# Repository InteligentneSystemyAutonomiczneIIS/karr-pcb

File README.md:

# karr-pcb
PCB for autonomus city simulation project

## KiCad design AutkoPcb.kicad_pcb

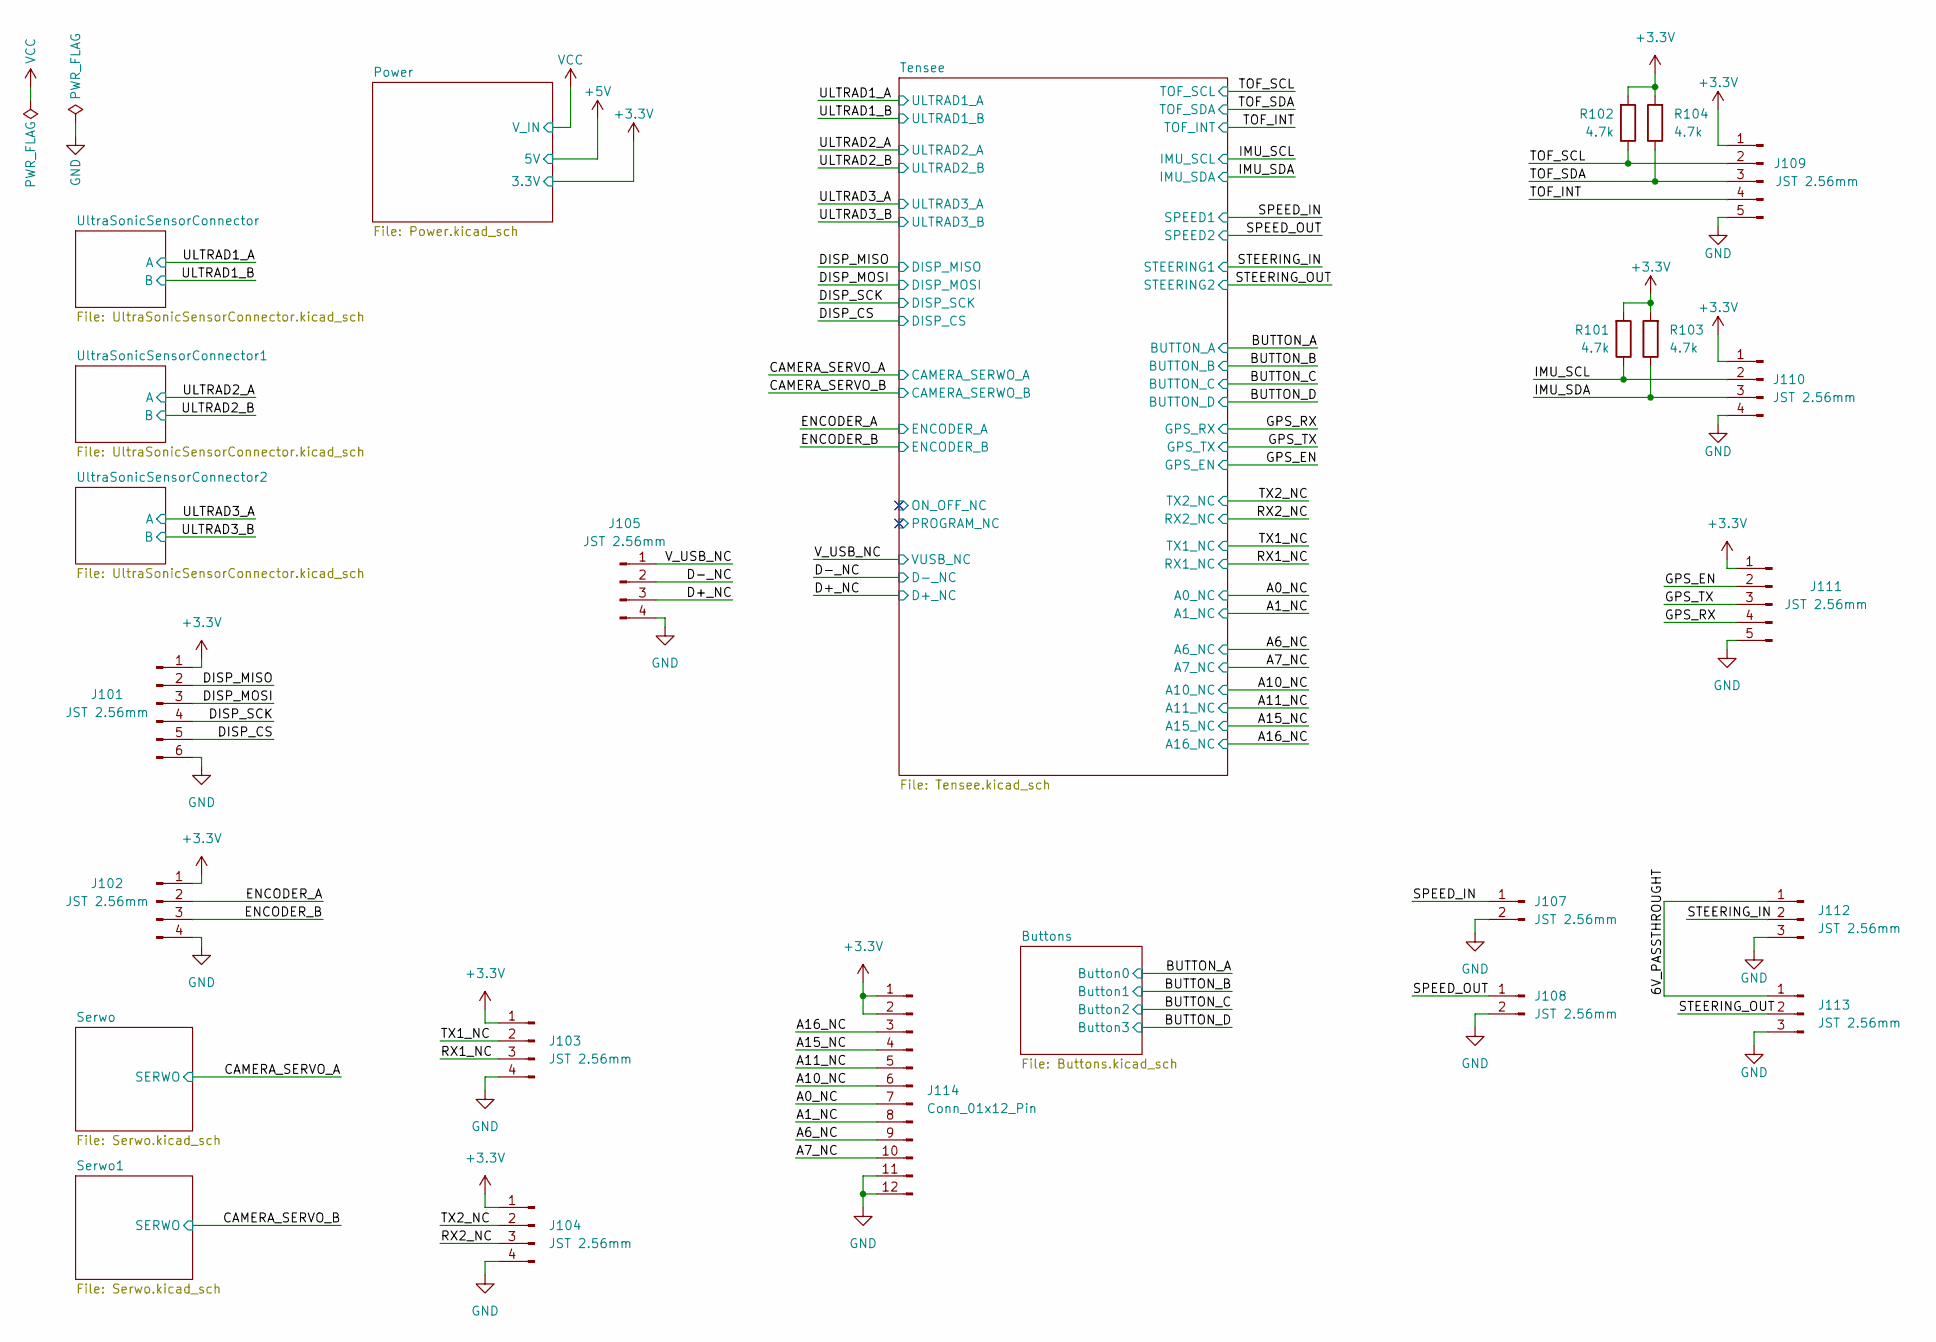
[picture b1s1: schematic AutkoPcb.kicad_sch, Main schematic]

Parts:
J101: JST 2.56mm; JST_XA_B06B-XASK-1_1x06_P2.50mm_Vertical
J102, J105, J110: JST 2.56mm; JST_XH_B4B-XH-A_1x04_P2.50mm_Vertical
J103, J104: JST 2.56mm; PinHeader_1x04_P2.54mm_Vertical
J107, J108: JST 2.56mm; JST_XH_B2B-XH-A_1x02_P2.50mm_Vertical
J109, J111: JST 2.56mm; JST_XH_B5B-XH-A_1x05_P2.50mm_Vertical
J112, J113: JST 2.56mm; JST_XH_B3B-XH-A_1x03_P2.50mm_Vertical
J114: Conn_01x12_Pin; PinSocket_1x12_P2.54mm_Vertical
R101, R102, R103, R104: 4.7k; R_Axial_DIN0204_L3.6mm_D1.6mm_P7.62mm_Horizontal

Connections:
+3.3V: J101.1, J102.1, J103.1, J104.1, J109.1, J110.1, J111.1, J114.1, J114.2, R101.2, R102.2, R103.2, R104.2; also elsewhere on the board
/6V_PASSTHROUGHT: J112.1, J113.1
/A0_NC: J114.7; also elsewhere on the board
/A1_NC: J114.8; also elsewhere on the board
/A6_NC: J114.9; also elsewhere on the board
/A7_NC: J114.10; also elsewhere on the board
/A10_NC: J114.6; also elsewhere on the board
/A11_NC: J114.5; also elsewhere on the board
/A15_NC: J114.4; also elsewhere on the board
/A16_NC: J114.3; also elsewhere on the board
/D+_NC: J105.3; also elsewhere on the board
/D-_NC: J105.2; also elsewhere on the board
/DISP_CS: J101.5; also elsewhere on the board
/DISP_MISO: J101.2; also elsewhere on the board
/DISP_MOSI: J101.3; also elsewhere on the board
/DISP_SCK: J101.4; also elsewhere on the board
/ENCODER_A: J102.2; also elsewhere on the board
/ENCODER_B: J102.3; also elsewhere on the board
/GPS_EN: J111.2; also elsewhere on the board
/GPS_RX: J111.4; also elsewhere on the board
/GPS_TX: J111.3; also elsewhere on the board
/IMU_SCL: J110.2, R101.1; also elsewhere on the board
/IMU_SDA: J110.3, R103.1; also elsewhere on the board
/RX1_NC: J103.3; also elsewhere on the board
/RX2_NC: J104.3; also elsewhere on the board
/SPEED_IN: J107.1; also elsewhere on the board
/SPEED_OUT: J108.1; also elsewhere on the board
/STEERING_IN: J112.2; also elsewhere on the board
/STEERING_OUT: J113.2; also elsewhere on the board
/TOF_INT: J109.4; also elsewhere on the board
/TOF_SCL: J109.2, R102.1; also elsewhere on the board
/TOF_SDA: J109.3, R104.1; also elsewhere on the board
/TX1_NC: J103.2; also elsewhere on the board
/TX2_NC: J104.2; also elsewhere on the board
/V_USB_NC: J105.1; also elsewhere on the board
GND: J101.6, J102.4, J103.4, J104.4, J105.4, J107.2, J108.2, J109.5, J110.4, J111.5, J112.3, J113.3, J114.11, J114.12; also elsewhere on the board

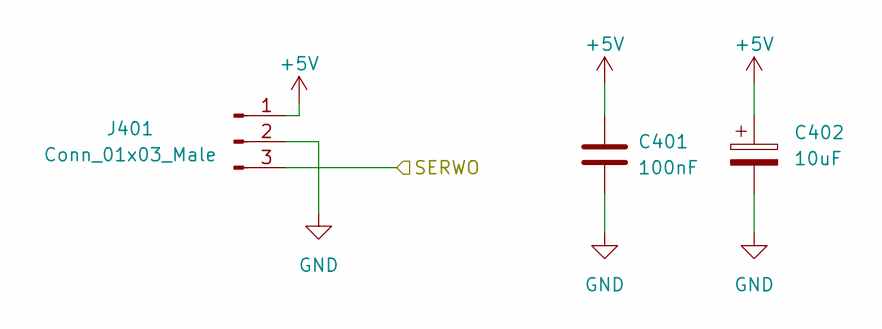
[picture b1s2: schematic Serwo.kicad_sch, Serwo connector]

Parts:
C401: 100nF; C_Disc_D3.0mm_W1.6mm_P2.50mm
C402: 10uF; CP_Radial_D5.0mm_P2.00mm
J401: Conn_01x03_Male; JST_XH_B3B-XH-A_1x03_P2.50mm_Vertical

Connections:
+5V: C401.1, C402.1, J401.1; also elsewhere on the board
/CAMERA_SERVO_A: J401.3; also elsewhere on the board
GND: C401.2, C402.2, J401.2; also elsewhere on the board

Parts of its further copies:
C501: 100nF; C_Disc_D3.0mm_W1.6mm_P2.50mm
C502: 10uF; CP_Radial_D5.0mm_P2.00mm
J501: Conn_01x03_Male; JST_XH_B3B-XH-A_1x03_P2.50mm_Vertical

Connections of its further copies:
+5V: C501.1, C502.1, J501.1; also elsewhere on the board
/CAMERA_SERVO_B: J501.3; also elsewhere on the board
GND: C501.2, C502.2, J501.2; also elsewhere on the board

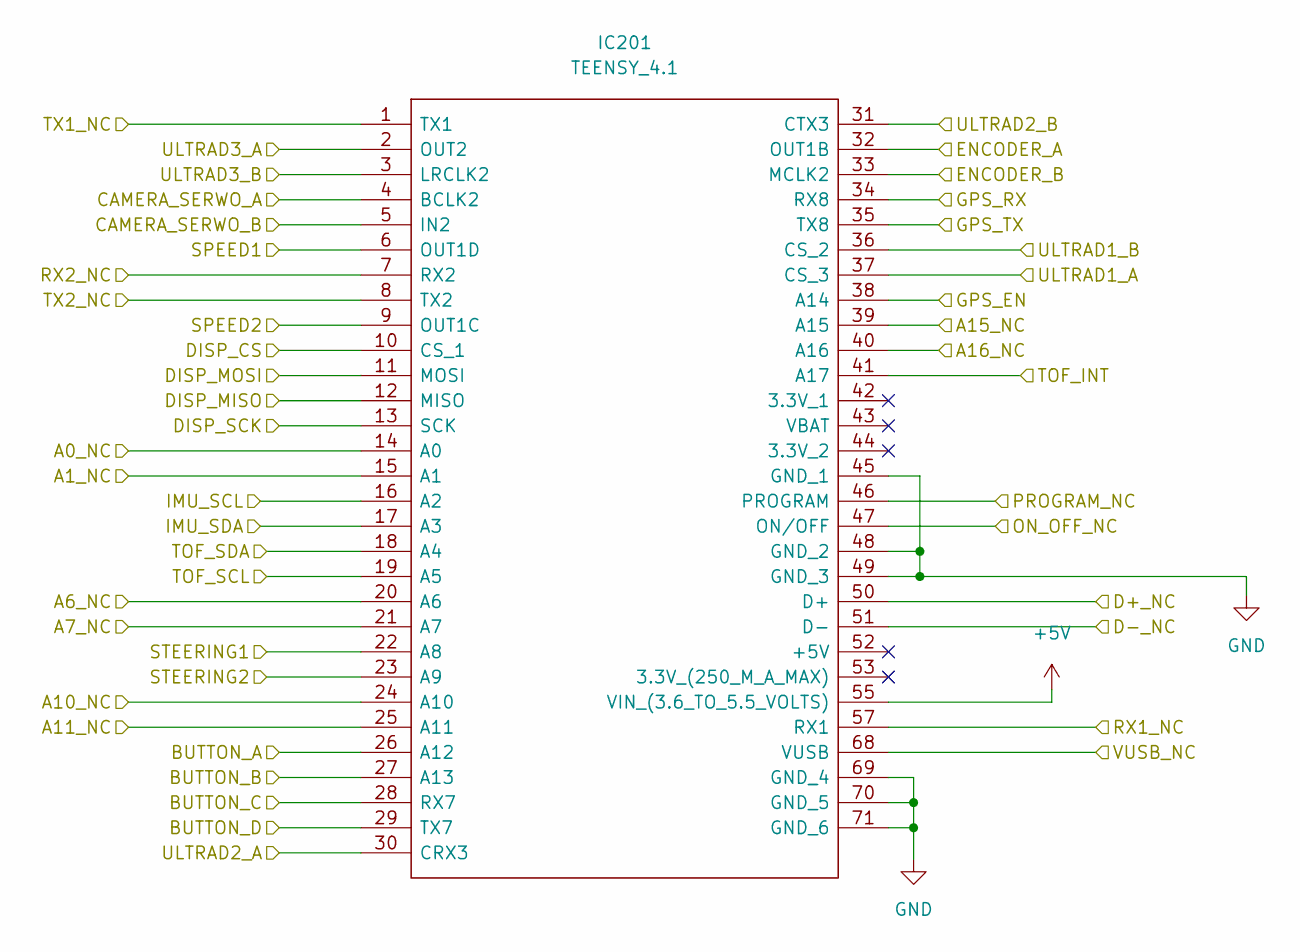
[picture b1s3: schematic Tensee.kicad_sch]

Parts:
IC201: TEENSY_4.1; TEENSY41; Manufacturer_Part_Number TEENSY 4.1

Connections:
+5V: IC201.55 (VIN_(3.6_TO_5.5_VOLTS)); also elsewhere on the board
/A0_NC: IC201.14 (A0); also elsewhere on the board
/A1_NC: IC201.15 (A1); also elsewhere on the board
/A6_NC: IC201.20 (A6); also elsewhere on the board
/A7_NC: IC201.21 (A7); also elsewhere on the board
/A10_NC: IC201.24 (A10); also elsewhere on the board
/A11_NC: IC201.25 (A11); also elsewhere on the board
/A15_NC: IC201.39 (A15); also elsewhere on the board
/A16_NC: IC201.40 (A16); also elsewhere on the board
/BUTTON_A: IC201.26 (A12); also elsewhere on the board
/BUTTON_B: IC201.27 (A13); also elsewhere on the board
/BUTTON_C: IC201.28 (RX7); also elsewhere on the board
/BUTTON_D: IC201.29 (TX7); also elsewhere on the board
/CAMERA_SERVO_A: IC201.4 (BCLK2); also elsewhere on the board
/CAMERA_SERVO_B: IC201.5 (IN2); also elsewhere on the board
/D+_NC: IC201.50 (D+); also elsewhere on the board
/D-_NC: IC201.51 (D-); also elsewhere on the board
/DISP_CS: IC201.10 (CS_1); also elsewhere on the board
/DISP_MISO: IC201.12 (MISO); also elsewhere on the board
/DISP_MOSI: IC201.11 (MOSI); also elsewhere on the board
/DISP_SCK: IC201.13 (SCK); also elsewhere on the board
/ENCODER_A: IC201.32 (OUT1B); also elsewhere on the board
/ENCODER_B: IC201.33 (MCLK2); also elsewhere on the board
/GPS_EN: IC201.38 (A14); also elsewhere on the board
/GPS_RX: IC201.34 (RX8); also elsewhere on the board
/GPS_TX: IC201.35 (TX8); also elsewhere on the board
/IMU_SCL: IC201.16 (A2); also elsewhere on the board
/IMU_SDA: IC201.17 (A3); also elsewhere on the board
/RX1_NC: IC201.57 (RX1); also elsewhere on the board
/RX2_NC: IC201.7 (RX2); also elsewhere on the board
/SPEED_IN: IC201.6 (OUT1D); also elsewhere on the board
/SPEED_OUT: IC201.9 (OUT1C); also elsewhere on the board
/STEERING_IN: IC201.22 (A8); also elsewhere on the board
/STEERING_OUT: IC201.23 (A9); also elsewhere on the board
/TOF_INT: IC201.41 (A17); also elsewhere on the board
/TOF_SCL: IC201.19 (A5); also elsewhere on the board
/TOF_SDA: IC201.18 (A4); also elsewhere on the board
/TX1_NC: IC201.1 (TX1); also elsewhere on the board
/TX2_NC: IC201.8 (TX2); also elsewhere on the board
/Tensee/ON_OFF_NC: IC201.47 (ON/OFF)
/Tensee/PROGRAM_NC: IC201.46 (PROGRAM)
/ULTRAD1_A: IC201.37 (CS_3); also elsewhere on the board
/ULTRAD1_B: IC201.36 (CS_2); also elsewhere on the board
/ULTRAD2_A: IC201.30 (CRX3); also elsewhere on the board
/ULTRAD2_B: IC201.31 (CTX3); also elsewhere on the board
/ULTRAD3_A: IC201.2 (OUT2); also elsewhere on the board
/ULTRAD3_B: IC201.3 (LRCLK2); also elsewhere on the board
/V_USB_NC: IC201.68 (VUSB); also elsewhere on the board
GND: IC201.45 (GND_1), IC201.48 (GND_2), IC201.49 (GND_3), IC201.69 (GND_4), IC201.70 (GND_5), IC201.71 (GND_6); also elsewhere on the board

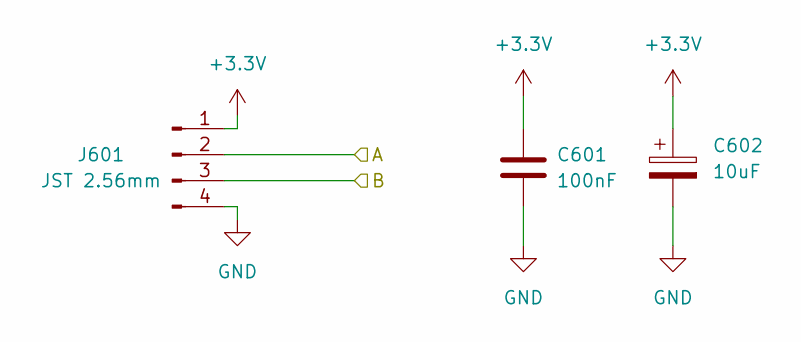
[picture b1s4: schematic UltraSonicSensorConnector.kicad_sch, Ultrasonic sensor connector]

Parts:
C601: 100nF; C_Disc_D3.0mm_W1.6mm_P2.50mm
C602: 10uF; CP_Radial_D5.0mm_P2.00mm
J601: JST 2.56mm; JST_XH_B4B-XH-A_1x04_P2.50mm_Vertical

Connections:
+3.3V: C601.1, C602.1, J601.1; also elsewhere on the board
/ULTRAD1_A: J601.2; also elsewhere on the board
/ULTRAD1_B: J601.3; also elsewhere on the board
GND: C601.2, C602.2, J601.4; also elsewhere on the board

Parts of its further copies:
C701, C801: 100nF; C_Disc_D3.0mm_W1.6mm_P2.50mm
C702, C802: 10uF; CP_Radial_D5.0mm_P2.00mm
J701, J801: JST 2.56mm; JST_XH_B4B-XH-A_1x04_P2.50mm_Vertical

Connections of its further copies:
+3.3V: C701.1, C702.1, C801.1, C802.1, J701.1, J801.1; also elsewhere on the board
/ULTRAD2_A: J701.2; also elsewhere on the board
/ULTRAD2_B: J701.3; also elsewhere on the board
/ULTRAD3_A: J801.2; also elsewhere on the board
/ULTRAD3_B: J801.3; also elsewhere on the board
GND: C701.2, C702.2, C801.2, C802.2, J701.4, J801.4; also elsewhere on the board

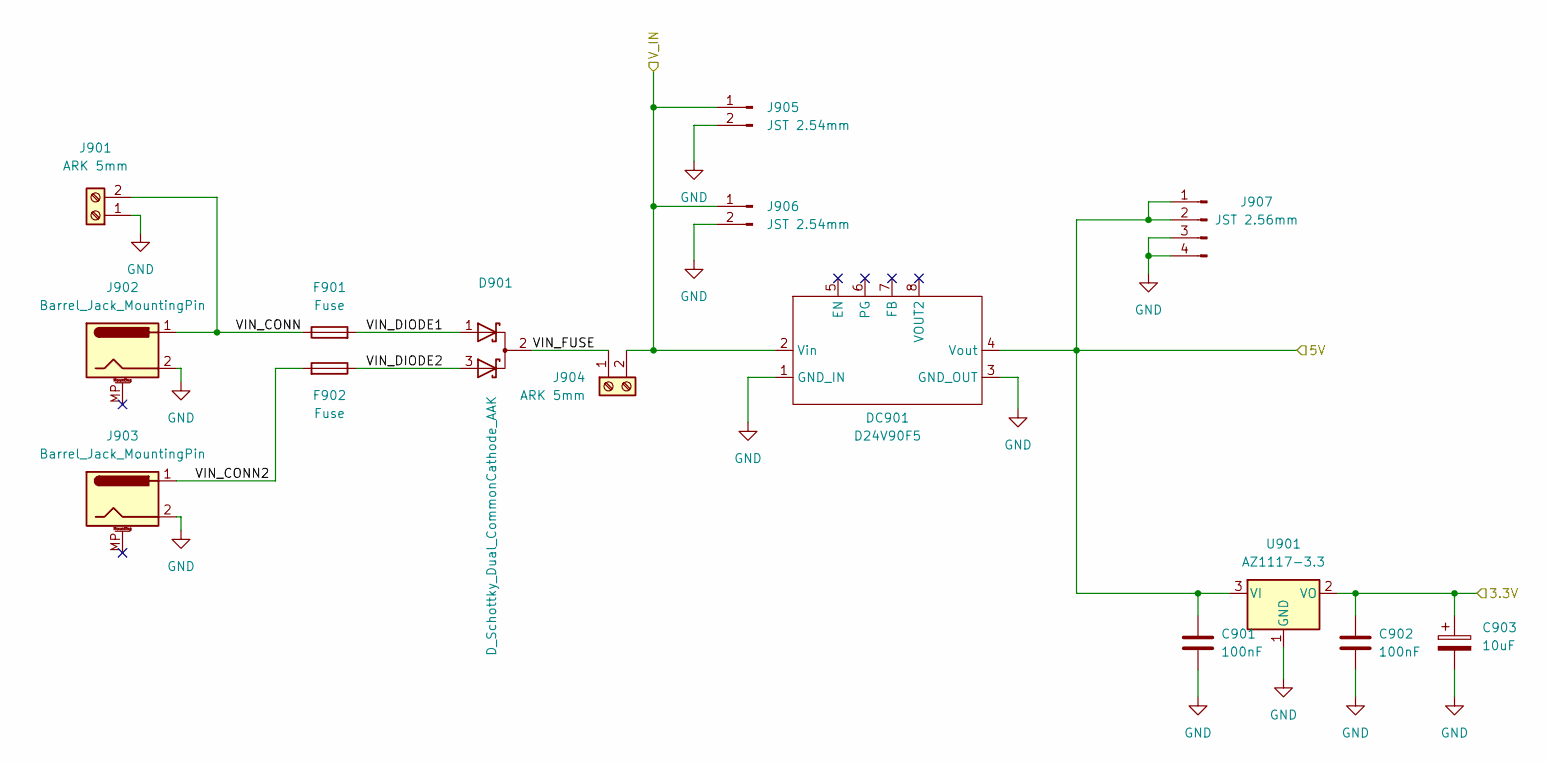
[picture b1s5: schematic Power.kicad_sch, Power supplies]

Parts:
C901, C902: 100nF; C_Disc_D3.0mm_W1.6mm_P2.50mm
C903: 10uF; CP_Radial_D5.0mm_P2.00mm
D901: D_Schottky_Dual_CommonCathode_AAK; TO-220-3_Vertical
DC901: D24V90F5
F901, F902: Fuse; Fuse_Bourns_MF-RHT1000
J901, J904: ARK 5mm; TerminalBlock_Philmore_TB132_1x02_P5.00mm_Horizontal
J902, J903: Barrel_Jack_MountingPin; BarrelJack_Horizontal
J905, J906: JST 2.54mm; JST_XH_B2B-XH-A_1x02_P2.50mm_Vertical
J907: JST 2.56mm; JST_XH_B4B-XH-A_1x04_P2.50mm_Vertical
U901: AZ1117-3.3; TO-220-3_Horizontal_TabDown

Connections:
+3.3V: C902.1, C903.1, U901.2 (VO); also elsewhere on the board
+5V: C901.1, DC901.4 (Vout), J907.1, J907.2, U901.3 (VI); also elsewhere on the board
/Power/VIN_CONN: F901.1, J901.2, J902.1
/Power/VIN_CONN2: F902.2, J903.1
/Power/VIN_DIODE1: D901.1 (K), F901.2
/Power/VIN_DIODE2: D901.3 (K), F902.1
/Power/VIN_FUSE: D901.2 (A), J904.1
GND: C901.2, C902.2, C903.2, DC901.1 (GND_IN), DC901.3 (GND_OUT), J901.1, J902.2, J903.2, J905.2, J906.2, J907.3, J907.4, U901.1 (GND); also elsewhere on the board
VCC: DC901.2 (Vin), J904.2, J905.1, J906.1

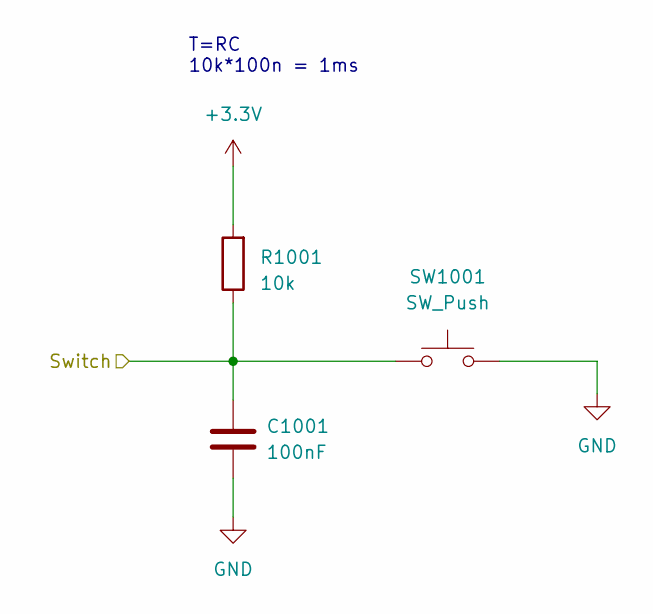
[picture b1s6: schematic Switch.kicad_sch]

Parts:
C1001: 100nF; C_Disc_D3.0mm_W1.6mm_P2.50mm
R1001: 10k; R_Axial_DIN0204_L3.6mm_D1.6mm_P7.62mm_Horizontal
SW1001: SW_Push; Tact Switch 6x6mm 5mm

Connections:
+3.3V: R1001.2; also elsewhere on the board
/BUTTON_A: C1001.1, R1001.1, SW1001.1; also elsewhere on the board
GND: C1001.2, SW1001.2; also elsewhere on the board

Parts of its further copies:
C1101, C1201, C1301: 100nF; C_Disc_D3.0mm_W1.6mm_P2.50mm
R1101, R1201, R1301: 10k; R_Axial_DIN0204_L3.6mm_D1.6mm_P7.62mm_Horizontal
SW1101, SW1201, SW1301: SW_Push; Tact Switch 6x6mm 5mm

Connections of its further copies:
+3.3V: R1101.2, R1201.2, R1301.2; also elsewhere on the board
/BUTTON_B: C1101.1, R1101.1, SW1101.1; also elsewhere on the board
/BUTTON_C: C1201.1, R1201.1, SW1201.1; also elsewhere on the board
/BUTTON_D: C1301.1, R1301.1, SW1301.1; also elsewhere on the board
GND: C1101.2, C1201.2, C1301.2, SW1101.2, SW1201.2, SW1301.2; also elsewhere on the board

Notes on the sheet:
T=RC 10k*100n = 1ms

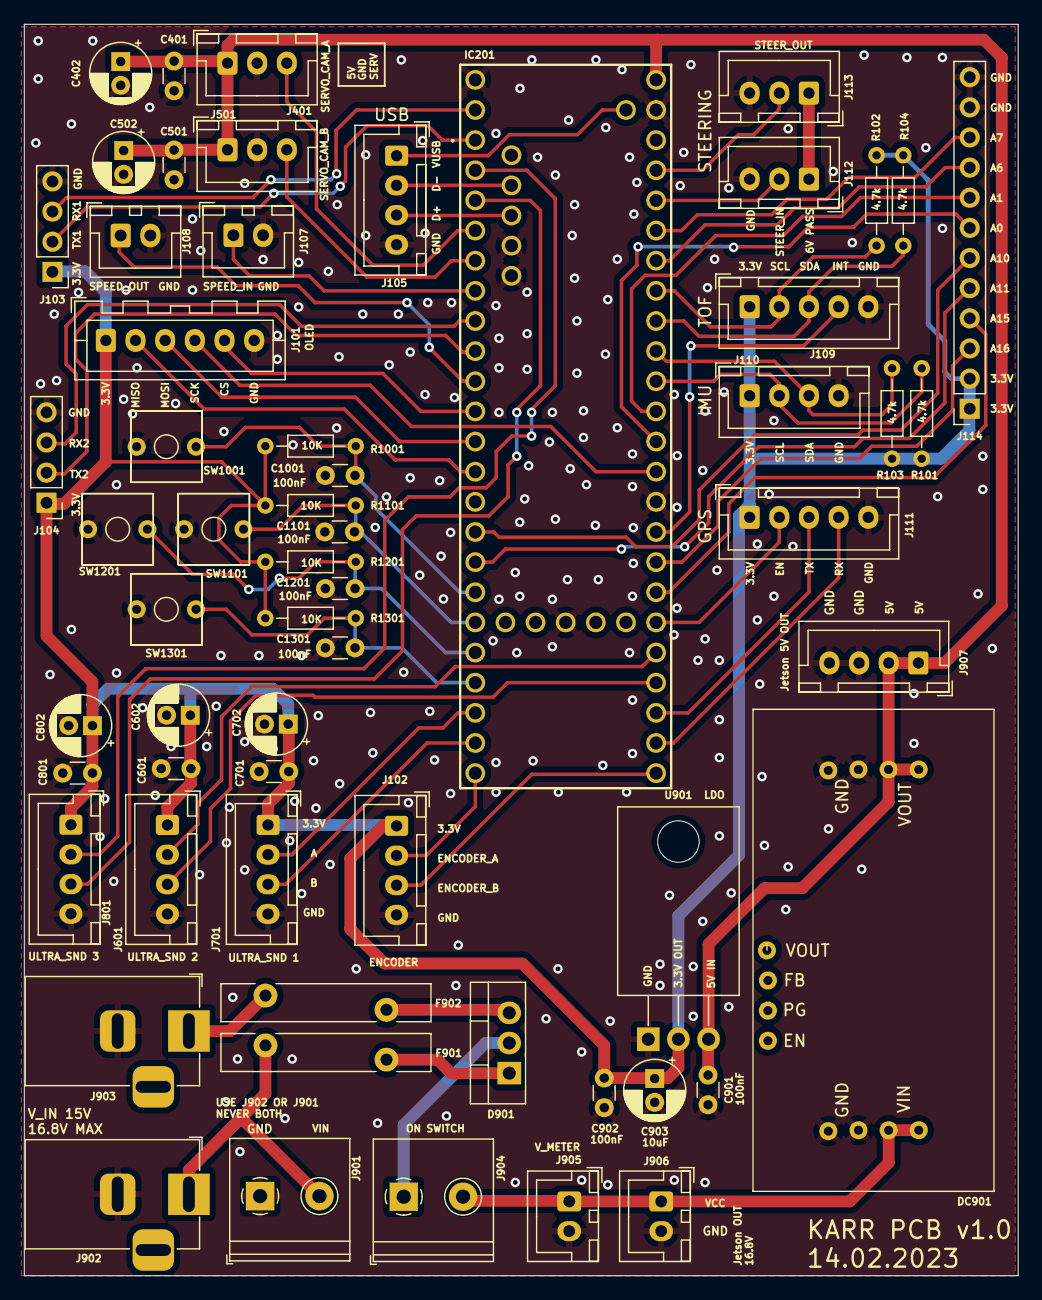
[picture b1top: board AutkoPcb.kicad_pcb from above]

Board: 2 copper layers, 83.8 x 105.5 mm, 60 parts (0 on the bottom side), 55 nets.

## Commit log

2023-01-22 added schematic nearly finished
2023-01-25 initial PCB layout is done
2023-02-02 [FEAT] schematic and alyout finished but need to be revieved
2023-02-02 [FEAT] updated schematic, added ibom
2023-02-02 [FIX] changed type of barrel jack to correct one
2023-03-02 update plików
2023-03-08 schematic update after meeting
2023-03-17 layout update moved power section to the bottom of the board, ibom generated, changed footprint for switches
2023-03-28 final board candidate
2023-03-28 final board candidate 2
2023-03-31 changing labels on PCB
2023-04-13 [FEAT] Zaktualizowano układ do debauncing
2023-04-14 release
2023-04-14 gerber rerun
